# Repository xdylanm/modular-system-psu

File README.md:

# Modular System PSU

A PSU for a modular Eurorack system, featuring +/-12V and 5V rails, USB-C input, and a regulated USB-A output.

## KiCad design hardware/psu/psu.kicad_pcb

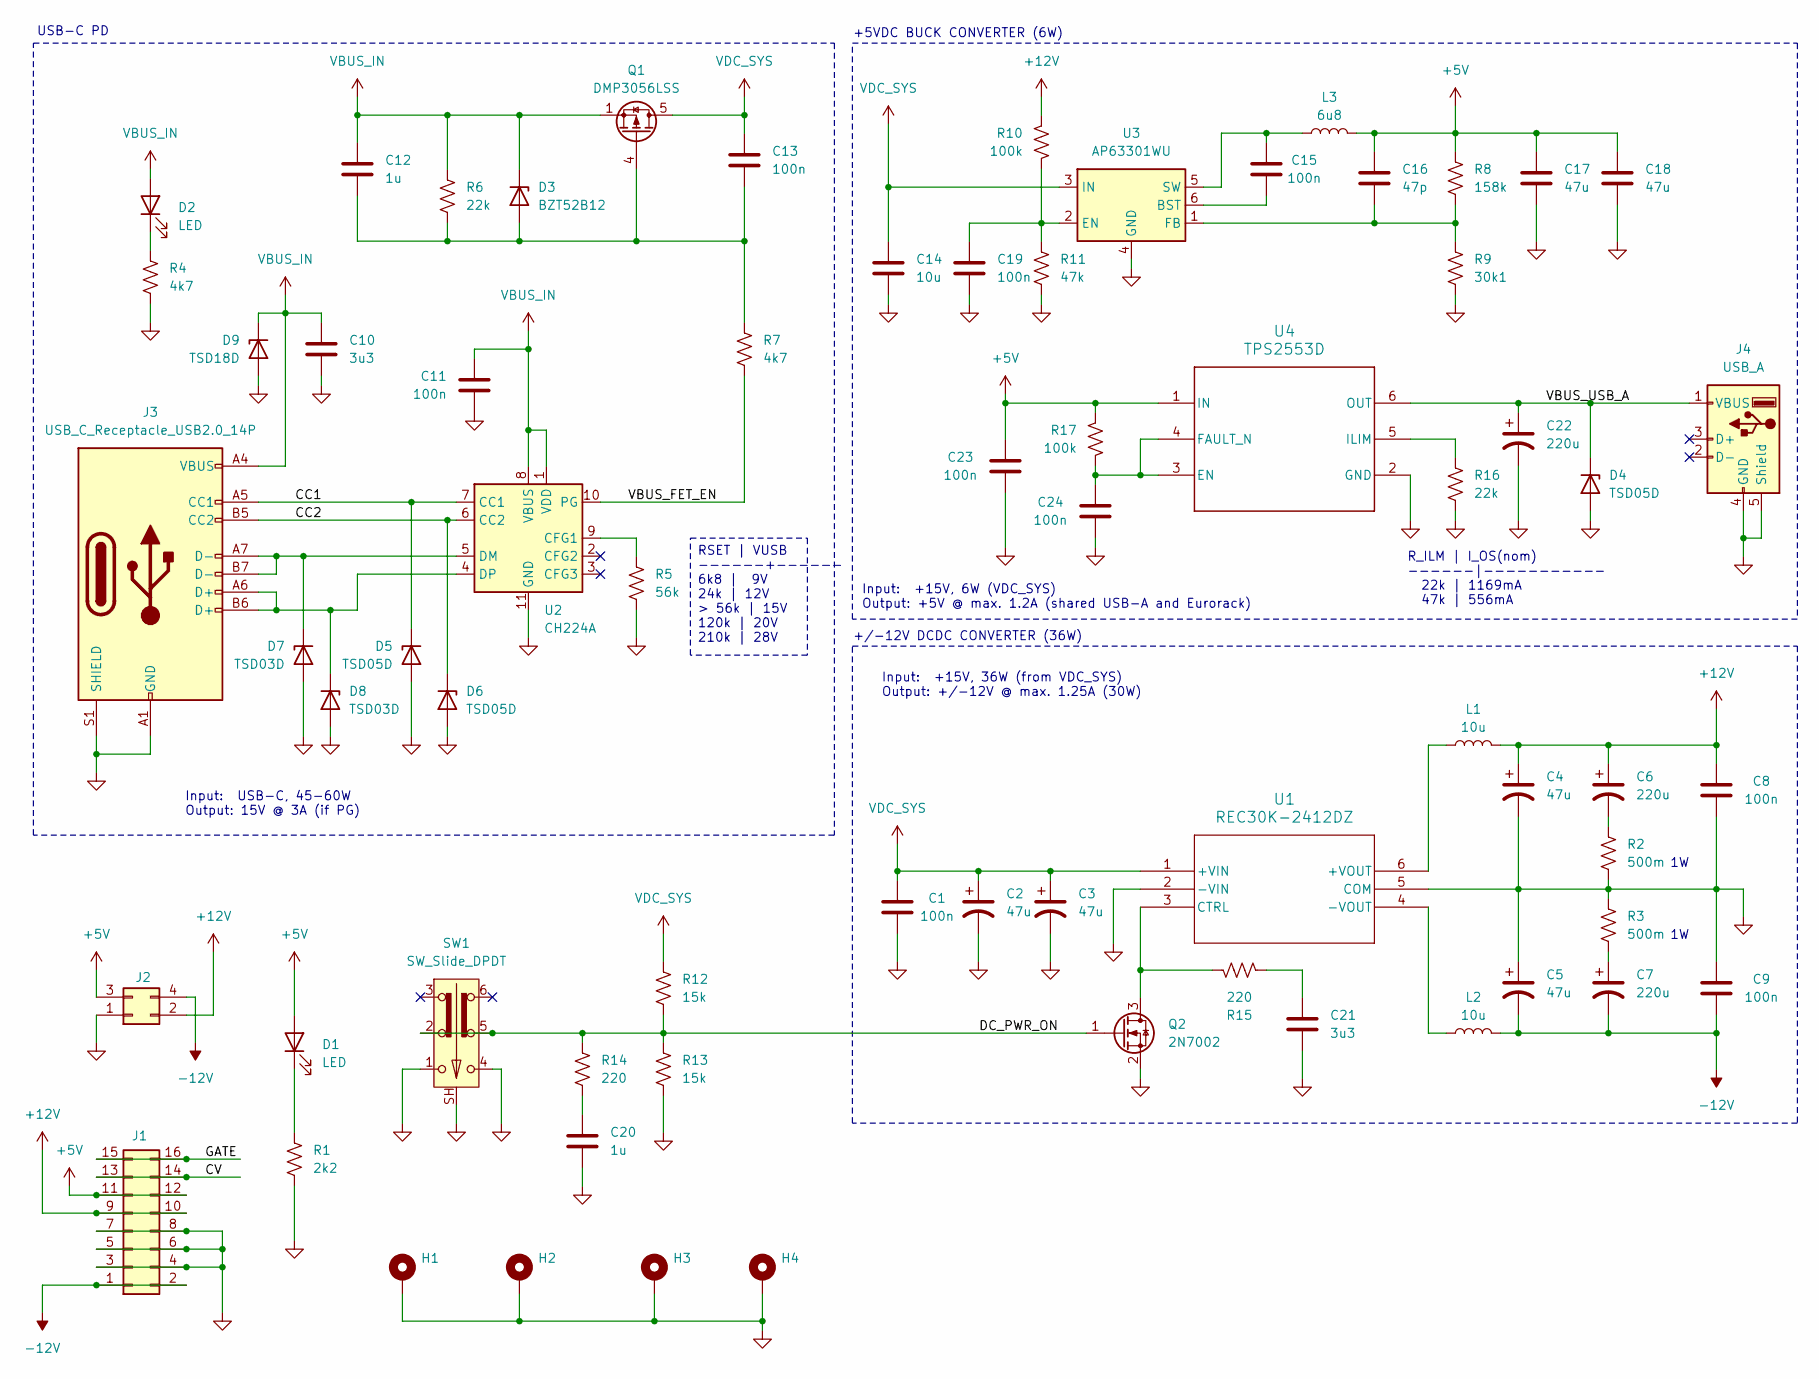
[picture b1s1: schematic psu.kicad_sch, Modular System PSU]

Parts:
C1, C8, C9, C11, C13, C15, C19, C23, C24: 100n; C_0805_2012Metric_Pad1.18x1.45mm_HandSolder
C2, C3, C4, C5: 47u; CAP_UCD_5X5P8_NCH
C6, C7, C22: 220u; CAP_UCD_6P3X7P7_NCH
C10, C21: 3u3; C_0805_2012Metric_Pad1.18x1.45mm_HandSolder
C12, C20: 1u; C_0805_2012Metric_Pad1.18x1.45mm_HandSolder
C14: 10u; C_1206_3216Metric_Pad1.33x1.80mm_HandSolder
C16: 47p; C_0805_2012Metric_Pad1.18x1.45mm_HandSolder
C17, C18: 47u; C_1206_3216Metric_Pad1.33x1.80mm_HandSolder
D1: LED; LED_D3.0mm
D2: LED; LED_0805_2012Metric_Pad1.15x1.40mm_HandSolder
D3: BZT52B12; D_SOD-123F
D4, D5, D6: TSD05D; D_SOD-323_HandSoldering
D7, D8: TSD03D; D_SOD-323_HandSoldering
D9: TSD18D; D_SOD-323_HandSoldering
H1, H2, H3, H4: MountingHole_Pad; MountingHole_3.2mm_M3_Pad_Via
J1: Conn_02x08_Odd_Even; IDC-Header_2x08_P2.54mm_Horizontal
J2: Conn_02x02_Odd_Even; Molex_Micro-Fit_3.0_43045-0400_2x02_P3.00mm_Horizontal
J3: USB_C_Receptacle_USB2.0_14P; USB_C_Receptacle_Samesky_UJ20-C-R-G-TH-1-P14-TR
J4: USB_A; USB_A_Receptacle_OST_A1HSW6
L1, L2: 10u; IND_BOURNS_SRR6038
L3: 6u8; IND_MGAH06036R8M-10
Q1: DMP3056LSS; SO-8_3.9x4.9mm_P1.27mm
Q2: 2N7002; SOT-23
R1: 2k2; R_0805_2012Metric_Pad1.20x1.40mm_HandSolder
R2, R3: 500m; R_1206_3216Metric_Pad1.30x1.75mm_HandSolder
R4, R7: 4k7; R_0805_2012Metric_Pad1.20x1.40mm_HandSolder
R5: 56k; R_0805_2012Metric_Pad1.20x1.40mm_HandSolder
R6, R16: 22k; R_0805_2012Metric_Pad1.20x1.40mm_HandSolder
R8: 158k; R_0805_2012Metric_Pad1.20x1.40mm_HandSolder
R9: 30k1; R_0805_2012Metric_Pad1.20x1.40mm_HandSolder
R10, R17: 100k; R_0805_2012Metric_Pad1.20x1.40mm_HandSolder
R11: 47k; R_0805_2012Metric_Pad1.20x1.40mm_HandSolder
R12, R13: 15k; R_0805_2012Metric_Pad1.20x1.40mm_HandSolder
R14, R15: 220; R_0805_2012Metric_Pad1.20x1.40mm_HandSolder
SW1: SW_Slide_DPDT; SW_DPDT_LC2255EENP
U1: REC30K-2412DZ; Converter_DCDC_REC30K-2412DZ
U2: CH224A; SSOP-10-1EP_3.9x4.9mm_P1mm_EP2.1x3.3mm
U3: AP63301WU; TSOT-23-6
U4: TPS2553D; SOT-23-6_Handsoldering

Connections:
+5V: C16.1, C17.1, C18.1, C23.2, D1.2 (A), J1.11, J1.12, J2.3, L3.2, R8.1, R17.1, U4.1 (IN)
+12V: C4.1, C6.1, C8.2, J1.9, J1.10, J2.2, L1.2, R10.1
-12V: C5.2, C7.2, C9.1, J1.1, J1.2, J2.4, L2.2
/CC1: D5.1 (K), J3.A5 (CC1), U2.7 (CC1)
/CC2: D6.1 (K), J3.B5 (CC2), U2.6 (CC2)
/CV: J1.13, J1.14
/DC_PWR_ON: Q2.1 (G), R12.2, R13.1, R14.1, SW1.2 (B), SW1.5 (B)
/GATE: J1.15, J1.16
/VBUS_FET_EN: R7.2, U2.10 (PG)
/VBUS_USB_A: C22.1, D4.1 (K), J4.1 (VBUS), U4.6 (OUT)
GND: C1.1, C2.2, C3.2, C4.2, C5.1, C8.1, C9.2, C10.2, C11.2, C14.2, C17.2, C18.2, C19.1, C20.1, C21.1, C22.2, C23.1, C24.1, D4.2 (A), D5.2 (A), D6.2 (A), D7.2 (A), D8.2 (A), D9.2 (A), H1.1, H2.1, H3.1, H4.1, J1.3, J1.4, J1.5, J1.6, J1.7, J1.8, J2.1, J3.A1 (GND), J3.A12 (GND), J3.B1 (GND), J3.B12 (GND), J3.S1 (SHIELD), J4.4 (GND), J4.5 (Shield), Q2.2 (S), R1.2, R2.2, R3.1, R4.2, R5.2, R9.2, R11.2, R13.2, R16.2, SW1.1 (A), SW1.4 (A), SW1.SH (A), U1.2 (-VIN), U1.5 (COM), U2.11 (GND), U3.4 (GND), U4.2 (GND)
unnamed: C6.2, R2.1
unnamed: C7.1, R3.2
unnamed: C20.2, R14.2
unnamed: C21.2, R15.2
unnamed: D1.1 (K), R1.1
unnamed: D2.1 (K), R4.1
unnamed: C12.2, C13.2, D3.2 (A), Q1.4 (G), R6.2, R7.1
unnamed: D7.1 (K), J3.A7 (D-), J3.B7 (D-), U2.5 (DM)
unnamed: D8.1 (K), J3.A6 (D+), J3.B6 (D+), U2.4 (DP)
unnamed: Q2.3 (D), R15.1, U1.3 (CTRL)
unnamed: L1.1, U1.6 (+VOUT)
unnamed: L2.1, U1.4 (-VOUT)
unnamed: R5.1, U2.9 (CFG1)
unnamed: C15.1, U3.6 (BST)
unnamed: C19.2, R10.2, R11.1, U3.2 (EN)
unnamed: C16.2, R8.2, R9.1, U3.1 (FB)
unnamed: C15.2, L3.1, U3.5 (SW)
unnamed: C24.2, R17.2, U4.3 (EN), U4.4 (FAULT_N)
unnamed: R16.1, U4.5 (ILIM)
VBUS_IN: C10.1, C11.1, C12.1, D2.2 (A), D3.1 (K), D9.1 (K), J3.A4 (VBUS), J3.A9 (VBUS), J3.B4 (VBUS), J3.B9 (VBUS), Q1.1 (S), Q1.2 (S), Q1.3 (S), R6.1, U2.1 (VDD), U2.8 (VBUS)
VDC_SYS: C1.2, C2.1, C3.1, C13.1, C14.1, Q1.5 (D), Q1.6 (D), Q1.7 (D), Q1.8 (D), R12.1, U1.1 (+VIN), U3.3 (IN)

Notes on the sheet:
Input: +15V, 36W (from VDC_SYS) Output: +/-12V @ max. 1.25A (30W)
Input: +15V, 6W (VDC_SYS) Output: +5V @ max. 1.2A (shared USB-A and Eurorack)
Input: USB-C, 45-60W Output: 15V @ 3A (if PG)
+5VDC BUCK CONVERTER (6W)
USB-C PD
R_ILM | I_OS(nom) ------|----------- 22k | 1169mA 47k | 556mA
+/-12V DCDC CONVERTER (36W)
RSET | VUSB ------+------ 6k8 | 9V 24k | 12V > 56k | 15V 120k | 20V 210k | 28V

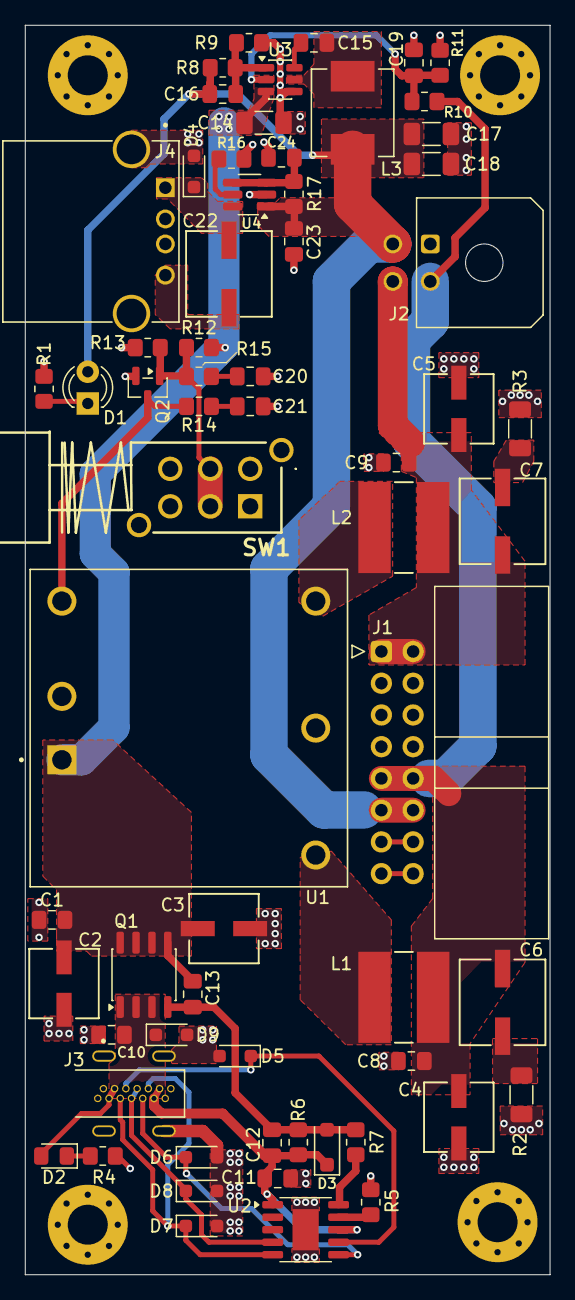
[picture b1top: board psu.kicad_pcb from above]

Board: 4 copper layers, 42.0 x 100.0 mm, 68 parts (0 on the bottom side), 32 nets.

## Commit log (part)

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2026-05-25 First board version, design docs and decisions, updated docs with archival version of old design
2026-05-25 Missed BOM files
2026-05-25 Doc updates: rendering math in notebooks, fixing image paths in notebooks, minor schematic tidyup (no changes to nets)
2026-05-25 docs: updated module size
2026-06-27 Version 1.1 board. Measurements complete, updated power on switch design, refined in-rush limiting

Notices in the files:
hardware/psu/psu.kicad_pcb:
CC BY-SA 4.0
idyllm CC BY-SA 4.0 v1.3.20261002
